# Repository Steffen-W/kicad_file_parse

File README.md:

# KiCad Parser

A comprehensive Python library for parsing and manipulating KiCad S-Expression files, including symbol libraries (.kicad_sym), footprints (.kicad_mod), worksheets (.kicad_wks), schematics (.kicad_sch), PCBs (.kicad_pcb), and related formats.

## Features

- **Full KiCad Format Support**: Parse and write KiCad symbol libraries, footprints, worksheets, schematics, and PCBs
- **Type-Safe**: Complete type hints for better IDE support and code safety
- **High-Level API**: Easy-to-use functions for common operations
- **Low-Level Access**: Direct access to S-expression data structures when needed
- **Multi-Unit Symbols**: Full support for complex symbols with multiple units and alternate representations
- **Advanced Pin Types**: Complete pin electrical type support (passive, input, output, bidirectional, tri_state, power_in, power_out, open_collector, open_emitter, free, unspecified, no_connect)
- **Hierarchical Schematics**: Support for hierarchical sheets, sheet pins, and complex project structures
- **Advanced PCB Features**: Zones with thermal reliefs and hatching patterns, advanced copper pours with complex fill settings, track arcs, board stackup definitions, and layer management
- **Modern Python**: Supports Python 3.8+
- **Zero Dependencies**: No external dependencies - includes bundled S-expression parser
- **Comprehensive Testing**: 385+ test cases ensuring reliability

## Installation

```bash
pip install kicad-parser
```

Or install from source:

```bash
git clone https://github.com/Steffen-W/kicad-parser.git
cd kicad-parser
pip install -e .
```

## Quick Start

### Loading and Modifying a Symbol Library

```python
from kicad_parser import load_symbol_library, save_symbol_library

# Load a KiCad symbol library
library = load_symbol_library("path/to/library.kicad_sym")

# Access symbols
symbol = library.symbols[0]
print(f"Symbol: {symbol.name}")

# Modify properties
symbol.set_property("Reference", "IC")
symbol.set_property("Description", "Modified with kicad-parser")

# Save changes
save_symbol_library(library, "path/to/modified_library.kicad_sym")
```

### Creating Symbols from Scratch

```python
from kicad_parser import (
    create_basic_symbol, KiCadSymbolLibrary, 
    SymbolPin, PinElectricalType, PinGraphicStyle, Position
)

# Create a new symbol library
library = KiCadSymbolLibrary(version=20211014, generator="kicad-parser")

# Create a basic resistor symbol
resistor = create_basic_symbol("R_Generic", "R", "R")

# Add pins
resistor.pins.extend([
    SymbolPin(
        electrical_type=PinElectricalType.PASSIVE,
        graphic_style=PinGraphicStyle.LINE,
        position=Position(-5.08, 0, 0),
        length=2.54,
        name="~",
        number="1"
    ),
    SymbolPin(
        electrical_type=PinElectricalType.PASSIVE,
        graphic_style=PinGraphicStyle.LINE,
        position=Position(5.08, 0, 0),
        length=2.54,
        name="~",
        number="2"
    )
])

# Add to library and save
library.add_symbol(resistor)
save_symbol_library(library, "custom_library.kicad_sym")
```

### Working with Footprints

```python
from kicad_parser import load_footprint, save_footprint, create_basic_footprint

# Load footprint
footprint = load_footprint("path/to/footprint.kicad_mod")

# Create basic footprint
new_footprint = create_basic_footprint("0805_Resistor", "R", "0805")

# Save footprint
save_footprint(new_footprint, "0805_resistor.kicad_mod")
```

### Working with Worksheets

```python
from kicad_parser import (
    load_worksheet, save_worksheet, create_basic_worksheet,
    KiCadWorksheet, WorksheetText, WorksheetRectangle, 
    Position, CornerType
)

# Load existing worksheet
worksheet = load_worksheet("path/to/worksheet.kicad_wks")

# Create basic worksheet
new_worksheet = create_basic_worksheet("My Project", "My Company")

# Create custom worksheet
custom_worksheet = KiCadWorksheet()

# Add title block rectangle
custom_worksheet.add_rectangle(
    WorksheetRectangle(
        start=Position(110.0, 5.0),
        end=Position(210.0, 35.0),
        corner=CornerType.RIGHT_BOTTOM
    )
)

# Add title text
custom_worksheet.add_text(
    WorksheetText(
        text="Project Title",
        position=Position(160.0, 20.0),
        corner=CornerType.RIGHT_BOTTOM,
        maxlen=25
    )
)

# Save worksheet
save_worksheet(custom_worksheet, "custom_worksheet.kicad_wks")
```

### Generating UUIDs

KiCad objects often require unique identifiers. Use the `generate_UUID()` function instead of creating UUIDs manually:

```python
from kicad_parser import generate_UUID, KiCadSchematic, TitleBlock

# Generate UUIDs for new objects
schematic = KiCadSchematic(
    uuid=generate_UUID(),
    title_block=TitleBlock(title="My Project")
)

# For groups, symbols, or other objects requiring UUIDs
group_id = generate_UUID()
symbol_uuid = generate_UUID()
```

**Note**: UUIDs are not generated automatically. Always use `generate_UUID()` when creating objects that require unique identifiers.

### Working with Schematics

```python
from kicad_parser import (
    load_schematic, save_schematic, create_basic_schematic,
    KiCadSchematic, Junction, Wire, Bus, SchematicSymbol,
    GlobalLabel, HierarchicalSheet, HierarchicalPin, 
    LabelShape, PinElectricalType, Position, UUID, Property, TitleBlock
)

# Load existing schematic
schematic = load_schematic("path/to/schematic.kicad_sch")

# Create basic schematic
new_schematic = create_basic_schematic("LED Blinker", "My Company")

# Create comprehensive schematic
custom_schematic = KiCadSchematic(
    title_block=TitleBlock(
        title="Custom Circuit",
        date="2024-01-01",
        revision="Rev 1.0"
    )
)

# Add junctions (connection points)
custom_schematic.junctions.append(
    Junction(
        position=Position(50.0, 50.0),
        diameter=0.36,
        uuid=UUID("junction-1")
    )
)

# Add wires (connections)
custom_schematic.wires.extend([
    Wire(
        points=[(25.4, 25.4), (50.0, 25.4)],
        uuid=UUID("wire-1")
    ),
    Wire(
        points=[(50.0, 25.4), (50.0, 50.0)],  
        uuid=UUID("wire-2")
    )
])

# Add components/symbols
custom_schematic.symbols.append(
    SchematicSymbol(
        library_id="Device:R",
        position=Position(75.0, 50.0),
        uuid=UUID("R1"),
        properties=[
            Property("Reference", "R1"),
            Property("Value", "10k"),
            Property("Footprint", "Resistor_SMD:R_0603_1608Metric")
        ]
    )
)

# Add global labels for cross-sheet connections
custom_schematic.global_labels.append(
    GlobalLabel(
        text="VCC",
        shape=LabelShape.INPUT,
        position=Position(25.4, 75.0),
        uuid=UUID("vcc-label")
    )
)

# Add hierarchical sheets for complex designs
power_sheet = HierarchicalSheet(
    position=Position(150.0, 100.0),
    size=(50.0, 40.0),
    sheet_name="Power Supply",
    file_name="power.kicad_sch",
    uuid=UUID("power-sheet")
)

# Add pins to hierarchical sheet
power_sheet.pins.append(
    HierarchicalPin(
        name="VCC_OUT",
        electrical_type=PinElectricalType.OUTPUT,
        position=Position(150.0, 110.0),
        uuid=UUID("vcc-out-pin")
    )
)

custom_schematic.sheets.append(power_sheet)

# Add bus connections for multi-signal connections
custom_schematic.buses.append(
    Bus(
        points=[(100.0, 150.0), (200.0, 150.0)],
        uuid=UUID("data-bus")
    )
)

# Save schematic
save_schematic(custom_schematic, "custom_circuit.kicad_sch")
```

### Working with PCBs (Boards)

```python
from kicad_parser import (
    load_pcb, save_pcb, create_basic_pcb,
    KiCadPCB, BoardLayer, BoardNet, GeneralSettings, Zone,
    TrackSegment, TrackVia, TrackArc, LayerType, ViaType, 
    PadConnection, UUID
)

# Load existing PCB
pcb = load_pcb("path/to/board.kicad_pcb")

# Create basic PCB
new_pcb = create_basic_pcb()

# Create comprehensive PCB
custom_pcb = KiCadPCB(
    version=20230121,
    generator="kicad-parser",
    general=GeneralSettings(thickness=1.6)
)

# Define standard layer stackup
layers = [
    BoardLayer(ordinal=0, canonical_name="F.Cu", layer_type=LayerType.SIGNAL, user_name="Front Copper"),
    BoardLayer(ordinal=31, canonical_name="B.Cu", layer_type=LayerType.SIGNAL, user_name="Back Copper"),
    BoardLayer(ordinal=36, canonical_name="B.SilkS", layer_type=LayerType.USER, user_name="B.Silkscreen"),
    BoardLayer(ordinal=37, canonical_name="F.SilkS", layer_type=LayerType.USER, user_name="F.Silkscreen"),
    BoardLayer(ordinal=44, canonical_name="Edge.Cuts", layer_type=LayerType.USER, user_name="Edge Cuts"),
]
custom_pcb.layers = layers

# Create nets
nets = [
    BoardNet(ordinal=0, name=""),  # Unconnected net
    BoardNet(ordinal=1, name="GND"),
    BoardNet(ordinal=2, name="VCC"),
    BoardNet(ordinal=3, name="SIGNAL_DATA"),
]
custom_pcb.nets = nets

# Add track segments (copper traces)
custom_pcb.track_segments.extend([
    TrackSegment(
        start=(10.0, 10.0),
        end=(20.0, 10.0),
        width=0.25,  # 0.25mm width
        layer="F.Cu",
        net=1,  # GND net
        uuid=UUID("track-gnd-1")
    ),
    TrackSegment(
        start=(10.0, 15.0),
        end=(20.0, 15.0),
        width=0.25,
        layer="F.Cu",
        net=2,  # VCC net
        uuid=UUID("track-vcc-1")
    )
])

# Add vias (layer connections)
custom_pcb.track_vias.extend([
    TrackVia(
        position=(15.0, 10.0),
        size=0.8,      # Via diameter
        drill=0.4,     # Drill diameter
        layers=("F.Cu", "B.Cu"),
        net=1,         # GND net
        via_type=ViaType.THROUGH,
        uuid=UUID("via-gnd-1")
    ),
    TrackVia(
        position=(15.0, 15.0),
        size=0.8,
        drill=0.4,
        layers=("F.Cu", "B.Cu"),
        net=2,         # VCC net
        via_type=ViaType.THROUGH,
        uuid=UUID("via-vcc-1")
    )
])

# Add copper zones/pours
custom_pcb.zones.append(
    Zone(
        net=1,  # GND net
        net_name="GND",
        layers=["F.Cu"],
        polygon_points=[
            (5.0, 5.0), (25.0, 5.0), (25.0, 25.0), (5.0, 25.0)
        ],
        connect_pads=PadConnection.THERMAL,
        min_thickness=0.254,
        uuid=UUID("ground-zone-1")
    )
)

# Add curved traces (track arcs)
custom_pcb.track_arcs.append(
    TrackArc(
        start=(30.0, 10.0),
        mid=(32.0, 12.0),
        end=(34.0, 10.0),
        width=0.25,
        layer="F.Cu",
        net=3,  # SIGNAL_DATA net
        uuid=UUID("arc-signal-1")
    )
)

# Save PCB
save_pcb(custom_pcb, "custom_board.kicad_pcb")
```

## API Reference

### High-Level Functions

#### File I/O

- `load_symbol_library(filepath)` → `KiCadSymbolLibrary`
- `save_symbol_library(library, filepath)` → `None`
- `load_footprint(filepath)` → `KiCadFootprint`
- `save_footprint(footprint, filepath)` → `None`
- `load_worksheet(filepath)` → `KiCadWorksheet`
- `save_worksheet(worksheet, filepath)` → `None`
- `load_schematic(filepath)` → `KiCadSchematic`
- `save_schematic(schematic, filepath)` → `None`
- `load_pcb(filepath)` → `KiCadPCB`
- `save_pcb(pcb, filepath)` → `None`
- `load_kicad_file(filepath)` → `KiCadObject` (auto-detects type)
- `save_kicad_file(obj, filepath)` → `None`

#### Creation Helpers

- `create_basic_symbol(name, reference, value)` → `KiCadSymbol`
- `create_basic_footprint(name, reference, value)` → `KiCadFootprint`
- `create_basic_worksheet(title, company)` → `KiCadWorksheet`
- `create_basic_schematic(title, company)` → `KiCadSchematic`
- `create_basic_pcb()` → `KiCadPCB`

#### Utilities

- `detect_file_type(content)` → `str`
- `validate_kicad_file(filepath)` → `dict`
- `convert_file(input_path, output_path, modifier_func=None)` → `None`
- `str_to_sexpr(content)` → `SExpr` - Convert string content to S-expression
- `sexpr_to_str(sexpr, pretty_print=True)` → `str` - Convert S-expression to formatted string
- `generate_UUID()` → `UUID` - Generate a new random UUID for KiCad objects

### Core Classes

#### Symbol Library (`KiCadSymbolLibrary`)

- `symbols: List[KiCadSymbol]` - List of symbols in library
- `version: int` - KiCad format version
- `generator: str` - Generator identifier
- `get_symbol(name)` → `Optional[KiCadSymbol]`
- `add_symbol(symbol)` → `None`
- `remove_symbol(name)` → `bool`

*Detailed S-expression format reference: [sexp-intro.md](doc/file-formats/sexp-intro.md)*

#### Symbol (`KiCadSymbol`)

- `name: str` - Symbol name
- `extends: Optional[str]` - Parent symbol for inheritance (symbol extends/parent support)
- `pin_numbers_hide: bool` - Hide pin numbers
- `pin_names_hide: bool` - Hide pin names  
- `pin_names_offset: float` - Pin name offset distance (advanced pin properties)
- `in_bom: bool` - Include in bill of materials
- `on_board: bool` - Export to PCB
- `properties: List[SymbolProperty]` - Symbol properties
- `pins: List[SymbolPin]` - Symbol pins with all electrical types
- `units: List[SymbolUnit]` - Symbol units for multi-unit symbols
- `rectangles: List[SymbolRectangle]` - Graphic rectangles
- `circles: List[SymbolCircle]` - Graphic circles
- `arcs: List[SymbolArc]` - Graphic arcs
- `beziers: List[SymbolBezier]` - Bézier curves
- `polylines: List[SymbolPolyline]` - Multi-point lines
- `texts: List[SymbolText]` - Text elements
- `get_property(key)` → `Optional[SymbolProperty]`
- `set_property(key, value, **kwargs)` → `None`
- `remove_property(key)` → `bool`

*Detailed S-expression format reference: [sexp-intro.md](doc/file-formats/sexp-intro.md)*

#### Footprint (`KiCadFootprint`)

- `library_link: str` - Link to symbol library
- `pads: List[FootprintPad]` - Footprint pads with custom primitives and complex shapes support
- `zones: List[Zone]` - Footprint-level copper zones
- `keepout_zones: List[Zone]` - Footprint keepout areas with configurable restrictions
- `groups: List[Group]` - Footprint object grouping for organization
- `net_tie_pad_groups: List[str]` - Net-tie pad group definitions for shorts allowed between pads
- `private_layers: List[str]` - Private layer definitions for footprint-specific layers
- `texts: List[FootprintText]` - Text elements
- `lines: List[FootprintLine]` - Graphic lines
- `rectangles: List[FootprintRectangle]` - Graphic rectangles
- `circles: List[FootprintCircle]` - Graphic circles
- `arcs: List[FootprintArc]` - Graphic arcs
- `polygons: List[FootprintPolygon]` - Graphic polygons
- `model: Footprint3DModel` - Advanced 3D model with positioning, scaling, rotation, opacity, and visibility control
- `position: Position` - Footprint position
- `layer: str` - Footprint placement layer
- `locked: bool` - Footprint lock status
- `attributes: FootprintAttributes` - Footprint attributes (SMD, through-hole, exclude from BOM/board)

*Detailed S-expression format reference: [sexp-intro.md](doc/file-formats/sexp-intro.md)*

#### Worksheet (`KiCadWorksheet`)

- `version: int` - KiCad format version
- `generator: str` - Generator identifier
- `setup: WorksheetSetup` - Page setup configuration
- `lines: List[WorksheetLine]` - Line elements
- `rectangles: List[WorksheetRectangle]` - Rectangle elements
- `polygons: List[WorksheetPolygon]` - Polygon elements
- `texts: List[WorksheetText]` - Title block text elements
- `bitmaps: List[WorksheetBitmap]` - Image elements
- `add_line(line)` → `None`
- `add_rectangle(rectangle)` → `None`
- `add_polygon(polygon)` → `None`
- `add_text(text)` → `None`
- `add_bitmap(bitmap)` → `None`

*Detailed S-expression format reference: [sexp-worksheet.md](doc/file-formats/sexp-worksheet.md)*

#### Schematic (`KiCadSchematic`)

- `version: int` - KiCad format version
- `generator: str` - Generator identifier
- `uuid: UUID` - Schematic unique identifier
- `page_settings: PageSettings` - Paper size and orientation
- `title_block: TitleBlock` - Title block information
- `lib_symbols: List[KiCadSymbol]` - Symbol library definitions
- `junctions: List[Junction]` - Connection junctions
- `no_connects: List[NoConnect]` - Unused pin markers
- `wires: List[Wire]` - Wire connections
- `buses: List[Bus]` - Bus connections
- `symbols: List[SchematicSymbol]` - Component instances
- `global_labels: List[GlobalLabel]` - Cross-sheet labels
- `hierarchical_labels: List[HierarchicalLabel]` - Sheet connection labels
- `local_labels: List[LocalLabel]` - Wire/bus labels
- `sheets: List[HierarchicalSheet]` - Sub-schematic sheets
- `texts: List[SchematicText]` - Text annotations
- `polylines: List[Polyline]` - Graphical lines
- `images: List[Image]` - Embedded images

*Detailed S-expression format reference: [sexp-schematic.md](doc/file-formats/sexp-schematic.md)*

### Data Types

#### Core S-Expression Types

- `Position(x, y, angle, layer)` - Position identifier with coordinates, rotation, and optional layer
- `CoordinatePoint(x, y)` - Single coordinate point with X/Y values
- `CoordinatePointList(points)` - Point list for polygons and curves with XY coordinate pairs
- `Stroke(width, type, color)` - Stroke definition with line styles, width, and color
- `StrokeType` - DEFAULT, NONE, SOLID, DASH, DOT, DASH_DOT, DASH_DOT_DOT - Line style types
- `TextEffects(font, justify, hide, mirror)` - Complete text formatting with alignment and visibility
- `Font(size, thickness, bold, italic, line_spacing, face)` - Font definition with all typography attributes
- `Fill(type, color)` - Fill definition with type and color
- `FillType` - NONE, OUTLINE, BACKGROUND - Fill style types
- `PageSettings(paper, width, height, portrait)` - Page configuration with size and orientation
- `TitleBlock(title, date, revision, company, comment_1_4)` - Title block with project information
- `Property(key, value, id, position, effects, show_name, do_not_autoplace)` - Properties with positioning and display control
- `UUID(uuid_string)` - Universally unique identifiers for object tracking
- `Image(position, scale, layer, data, uuid)` - Embedded PNG/bitmap images with positioning and Base64 data
- `Color(r, g, b, a)` - RGBA color definition with transparency support
- `Justify` - LEFT, CENTER, RIGHT, TOP, BOTTOM - Text alignment options
- `PaperSize` - A4, A3, A2, A1, A0, LETTER, LEGAL, TABLOID, USR - Standard paper sizes

#### Board-Specific Types

- `CANONICAL_LAYER_NAMES` - All 58 standard KiCad layers (F.Cu, B.Cu, F.SilkS, etc.)

#### Symbol Types

- `SymbolPin(electrical_type, graphic_style, position, length, name, number)` - Symbol pins with all electrical types
- `SymbolProperty(key, value, id, position, effects)` - Symbol properties with positioning
- `SymbolUnit(name, unit_id)` - Multi-unit symbol definitions for complex components
- `SymbolArc(start, mid, end, stroke, fill, uuid)` - Graphic arc elements
- `SymbolCircle(center, radius, stroke, fill, uuid)` - Graphic circle elements  
- `SymbolRectangle(start, end, stroke, fill, uuid)` - Graphic rectangle elements
- `SymbolBezier(points, stroke, fill, uuid)` - Bézier curve elements
- `SymbolPolyline(points, stroke, fill, uuid)` - Multi-point line elements
- `SymbolText(text, position, angle, effects, uuid)` - Text annotations and labels

#### Pin Types

- `PinElectricalType` - PASSIVE, INPUT, OUTPUT, BIDIRECTIONAL, TRI_STATE, POWER_IN, POWER_OUT, OPEN_COLLECTOR, OPEN_EMITTER, FREE, UNSPECIFIED, NO_CONNECT
- `PinGraphicStyle` - LINE, INVERTED, CLOCK, INVERTED_CLOCK, INPUT_LOW, CLOCK_LOW, OUTPUT_LOW, EDGE_CLOCK_HIGH, NONLOGIC

#### Footprint Types

- `FootprintPad(number, type, shape, size, drill, layers, position, net, uuid)` - Footprint pads with all pad types and shapes
- `FootprintText(type, text, position, layer, effects, uuid)` - Footprint text elements (reference, value, user)
- `FootprintLine(start, end, layer, width, uuid)` - Footprint graphic lines
- `FootprintRectangle(start, end, layer, stroke, fill, uuid)` - Footprint graphic rectangles
- `FootprintCircle(center, end, layer, stroke, fill, uuid)` - Footprint graphic circles
- `FootprintArc(start, mid, end, layer, stroke, uuid)` - Footprint graphic arcs
- `FootprintPolygon(points, layer, stroke, fill, uuid)` - Footprint graphic polygons
- `FootprintAttributes(type, board_only, exclude_from_pos_files, exclude_from_bom)` - Footprint placement attributes
- `FootprintOptions(clearance, solder_mask_margin, solder_paste_margin, zone_connect, thermal_width, thermal_gap)` - Advanced footprint options and clearances
- `CustomPadOptions(clearance, solder_mask_margin, solder_paste_margin, thermal_gap)` - Custom pad-specific options
- `FootprintPrimitives(primitives_list)` - Custom pad primitive shapes and geometries
- `CustomPadPrimitives(primitives_list)` - Advanced custom pad shape definitions
- `Net(code, name)` - Network connection definitions for pads
- `Drill(diameter, oval_width)` - Drill hole specifications with oval support
- `DrillDefinition(size, offset, shape)` - Complete drill definition with positioning
- `PadAttribute(type, value)` - Pad electrical and mechanical attributes
- `KeepoutSettings(tracks, vias, pads, copperpour, footprints)` - Keepout zone restrictions
- `KeepoutZone(layers, settings, polygon, uuid)` - Keepout areas with configurable restrictions
- `FootprintGroup(name, members, uuid)` - Footprint object grouping for organization
- `Model3D(filename, offset, scale, rotate)` - 3D model positioning and transformation
- `Footprint3DModel(filename, offset, scale, rotate, opacity, hide)` - 3D model with full control
- `FootprintType` - SMD, THROUGH_HOLE, EXCLUDE_FROM_POS_FILES, EXCLUDE_FROM_BOM - Footprint classifications
- `FootprintTextType` - REFERENCE, VALUE, USER - Text element types

#### Worksheet Types

- `WorksheetSetup(textsize, linewidth, textlinewidth, margins)` - Page setup with text sizes and margins
- `WorksheetLine(start, end, name, linewidth, repeat, increment)` - Lines with optional repetition and increments
- `WorksheetRectangle(start, end, name, linewidth, repeat, increment)` - Rectangles for borders and frames
- `WorksheetPolygon(points, name, linewidth, repeat, increment)` - Custom polygon shapes with coordinate points
- `WorksheetText(text, position, corner, name, maxlen, maxheight, font, justify)` - Title block text with positioning and limits
- `WorksheetBitmap(position, scale, data, name, repeat, increment)` - Embedded bitmap images with Base64 data
- `CornerType` - LEFT_TOP, LEFT_BOTTOM, RIGHT_BOTTOM, RIGHT_TOP - Position reference points

#### Schematic Types

- `Junction(position, diameter, color, uuid)` - Connection junction points
- `BusEntry(position, size, stroke, uuid)` - Bus connection entries with angle and direction
- `Wire(points, stroke, uuid)` - Electrical wire connections with multi-point routing
- `Bus(points, stroke, uuid)` - Multi-signal bus connections with stroke styling
- `SchematicText(text, position, effects, exclude_from_sim, uuid)` - Text annotations with simulation control
- `LocalLabel(text, position, effects, exclude_from_sim, uuid)` - Wire/bus name labels
- `GlobalLabel(text, shape, position, fields, properties, uuid)` - Cross-sheet labels with custom fields
- `HierarchicalLabel(text, shape, position, effects, uuid)` - Sheet connection labels
- `SchematicSymbol(library_id, position, unit, convert, exclude_from_sim, properties, instances)` - Component instances with simulation control
- `SheetInstance(path, page, uuid)` - Sheet instance definitions for hierarchical designs
- `SheetProject(file, name, description)` - Project information for sheet references
- `HierarchicalSheet(position, size, sheet_name, file_name, pins, project, instances, uuid)` - Sub-schematic sheets with project data
- `HierarchicalPin(name, electrical_type, position, uuid)` - Sheet connection pins
- `RootSheetInstance(project, page, uuid)` - Root sheet instance for project hierarchy
- `LabelShape` - INPUT, OUTPUT, BIDIRECTIONAL, TRI_STATE, PASSIVE - Label and pin shapes
- `NoConnect(position, uuid)` - Unused pin markers
- `Polyline(points, stroke, uuid)` - Graphical line drawings
- `Image(position, scale, layer, data, uuid)` - Embedded PNG images with Base64 data

#### PCB Types

- `KiCadPCB(version, generator, general, paper, layers, setup, nets, footprints, track_segments, track_vias, track_arcs, zones, groups)` - Complete PCB definition with all elements
- `GeneralSettings(thickness, legacy_teardrops)` - Board general settings and thickness
- `BoardLayer(ordinal, canonical_name, layer_type, user_name)` - PCB layer definition with all 58 standard layers
- `BoardSetup(stackup, design_rules, defaults, diff_pair_dimensions, pad_to_mask_clearance)` - Complete PCB setup with design rules and stackup
- `BoardNet(ordinal, name)` - Electrical net definition with net classes
- `TrackSegment(start, end, width, layer, net, tstamp, uuid)` - Copper trace segment with timestamps
- `TrackVia(position, size, drill, layers, net, via_type, remove_unused_layers, keep_end_layers, uuid)` - Via with advanced layer management
- `TrackArc(start, mid, end, width, layer, net, tstamp, uuid)` - Curved copper trace with arc geometry
- `Zone(net, net_name, layers, tstamp, name, hatch, priority, connect_pads, min_thickness, filled_polygons, fill_segments)` - Complete zone with fill geometry
- `ZoneConnect(clearance, min_thickness, thermal_gap, thermal_bridge_width)` - Zone connection settings
- `ZoneFillSettings(yes, mode, thermal_gap, thermal_bridge_width, smoothing, island_removal_mode, island_area_min)` - Zone fill configuration
- `Group(name, id, locked, members, uuid)` - Object grouping with locking and member tracking
- `Net(ordinal, name, uuid)` - Net definition with UUID tracking
- `Dimension(type, layer, tstamp, pts, height, orientation, leader_length, text_position, format, style, uuid)` - PCB dimensions and measurements
- `LayerType` - SIGNAL, POWER, MIXED, JUMPER, USER - Layer type classification
- `ViaType` - THROUGH, BLIND, MICRO - Via type specification with advanced drilling
- `PadConnection` - INHERITED, SOLID, THERMAL_RELIEFS, THRU_HOLE_ONLY, NONE - Zone connection styles
- `PadShape` - CIRCLE, RECT, OVAL, TRAPEZOID, ROUNDRECT, CUSTOM - Pad shape definitions
- `DrillShape` - CIRCLE, OVAL - Drill hole shapes

*Detailed S-expression format reference: [sexp-pcb.md](doc/file-formats/sexp-pcb.md)*

#### Design Rules Types

- `KiCadDesignRules(version, generator, rules)` - Complete design rules definition with all DRC rules
- `DesignRule(name, layer, constraint, condition, severity)` - Individual design rule with conditions and constraints
- `DesignRuleConstraint(type, value, opt_value, comment)` - Design rule constraint with value ranges
- `ConstraintValue(min, opt, max, units)` - Constraint value with optional minimum, optimal, and maximum values
- `ConstraintType` - CLEARANCE, TRACK_WIDTH, VIA_SIZE, DRILL_SIZE, LENGTH, SKEW, DISALLOW - Constraint classifications
- `DRCSeverity` - ERROR, WARNING, IGNORE, EXCLUSION - DRC violation severity levels

*Detailed S-expression format reference: [sexp-design-rules.md](doc/file-formats/sexp-design-rules.md)*

#### Graphics Types

- `GraphicalText(text, position, angle, layer, effects, uuid)` - Text elements with positioning and styling
- `GraphicalLine(start, end, layer, stroke, uuid)` - Straight line segments with stroke styling
- `GraphicalRectangle(start, end, layer, stroke, fill, uuid)` - Rectangle shapes with fill and stroke
- `GraphicalCircle(center, radius, layer, stroke, fill, uuid)` - Circle shapes with customizable appearance
- `GraphicalArc(start, mid, end, layer, stroke, uuid)` - Arc segments defined by three points
- `GraphicalPolygon(points, layer, stroke, fill, uuid)` - Multi-point polygon shapes
- `GraphicalBezier(points, layer, stroke, fill, uuid)` - Bézier curve segments for smooth curves
- `GraphicalTextBox(text, position, size, angle, layer, effects, stroke, uuid)` - Text with background box
- `Dimension(type, layer, pts, height, orientation, leader_length, format, style, uuid)` - PCB measurements and annotations
- `DimensionFormat(prefix, suffix, units, units_format, precision, suppress_zeros)` - Dimension text formatting
- `DimensionStyle(thickness, arrow_length, text_position_mode, extension_height, text_frame)` - Dimension appearance settings

#### Design Rules Types

- `KiCadDesignRules(version, generator, rules)` - Complete design rules definition with all DRC rules
- `DesignRule(name, layer, constraint, condition, severity)` - Individual design rule with conditions and constraints
- `DesignRuleConstraint(type, value, opt_value, comment)` - Design rule constraint with value ranges
- `ConstraintValue(min, opt, max, units)` - Constraint value with optional minimum, optimal, and maximum values
- `ConstraintType` - CLEARANCE, TRACK_WIDTH, VIA_SIZE, DRILL_SIZE, LENGTH, SKEW, DISALLOW - Constraint classifications
- `DRCSeverity` - ERROR, WARNING, IGNORE, EXCLUSION - DRC violation severity levels

## Examples

The `examples/` directory contains complete working examples:

- `basic_usage.py` - Loading, modifying, and saving symbol libraries
- `create_symbol.py` - Creating custom symbols and libraries from scratch
- `file_conversion.py` - File validation and conversion utilities
- `worksheet_example.py` - Creating custom worksheets and page layouts
- `schematic_example.py` - Creating comprehensive schematics with all element types
- `pcb_example.py` - Creating PCBs with layers, nets, tracks, and vias
- `file_comparison.py` - Comprehensive utility for comparing KiCad files
- `round_trip_test.py` - Parser accuracy validation through round-trip testing

### File Comparison Tool

A comprehensive utility for comparing KiCad files with multiple comparison modes and built-in demo functionality:

#### Comparison Modes

- **Exact Comparison**: Files must be completely identical (content, order, formatting)
- **Structural Comparison**: Same content, order doesn't matter (uses KiCad parser for semantic comparison)
- **Text Comparison**: Plain text comparison with optional whitespace normalization
- **Comprehensive Comparison**: Runs all methods and shows detailed results with similarity scores

#### Usage

```bash
# Command line usage
python examples/file_comparison.py file1.kicad_sch file2.kicad_sch

# Run without arguments to see interactive demo
python examples/file_comparison.py

# Programmatic usage
from examples.file_comparison import compare_files_exact, compare_files_structural
from kicad_parser.file_comparison_utils import ComparisonResult

result = compare_files_exact("file1.kicad_sch", "file2.kicad_sch")
print(f"Equal: {result.are_equal}, Similarity: {result.similarity_score:.2%}")

# Comprehensive comparison with detailed output
results = compare_files_comprehensive("original.kicad_sch", "modified.kicad_sch")
for method, result in results.items():
    print(f"{method}: {result}")
```

#### Available Functions

- `compare_files_exact()` → Perfect match comparison
- `compare_files_structural()` → Semantic content comparison  
- `compare_files_text()` → Text-based comparison with whitespace options
- `compare_files_comprehensive()` → All methods with detailed output

### Round-Trip Test

Validates parser accuracy by loading and re-saving KiCad files, then comparing the results:

```bash
# Run comprehensive accuracy test
python examples/round_trip_test.py

# Output shows parser fidelity:
# ROUND-TRIP TEST SUMMARY
# Accuracy Results:
#    Exact Match: 1/22 perfect (4.5%), avg similarity: 9.1%
#    Structural: 20/22 perfect (90.9%), avg similarity: 97.2%
#    Text (with whitespace): 1/22 perfect (4.5%), avg similarity: 9.1%
#    Text (normalized): 1/22 perfect (4.5%), avg similarity: 16.2%
```

This example demonstrates the high fidelity of the KiCad parser by testing all files in `examples/test_data/` and reporting conversion accuracy statistics.

Run examples:

```bash
cd examples
python basic_usage.py
python create_symbol.py
python file_conversion.py
python worksheet_example.py
python schematic_example.py
python file_comparison.py  # Runs demo automatically
python round_trip_test.py  # Validates parser accuracy
```

## Development

### Setup Development Environment

```bash
git clone https://github.com/Steffen-W/kicad-parser.git
cd kicad-parser
pip install -e ".[dev]"
```

### Running Tests

```bash
# Run all tests
pytest

# Run with coverage
pytest --cov=kicad_parser

# Generate coverage report
pytest --cov=kicad_parser --cov-report=html
pytest --cov=kicad_parser --cov-report=term-missing
```

### Documentation

Generate API documentation with Sphinx:

```bash
pip install -e .[docs]
python docs/build-docs.py
```

Open `docs/_build/html/index.html` in your browser. Use `python docs/build-docs.py pdf` for other formats.

### Code Quality

```bash
# Install required tools
pip install black isort flake8 mypy
npm install -g pyright

# Format entire codebase with black
black .

# Sort imports for entire codebase
isort .

# Lint code with flake8
flake8 kicad_parser

# Static type checking with Pyright
pyright

# Static type checking with mypy
mypy kicad_parser
```

## Implementation Reference

This library was developed based on the official KiCad S-Expression file format documentation:
**<https://dev-docs.kicad.org/en/file-formats/sexpr-intro/index.html>**

The data schema for parsing KiCad files is sourced from:
**<https://gitlab.com/kicad/services/kicad-dev-docs/-/tree/master/content/file-formats>**

The DRC (Design Rule Checking) implementation is based on:
**<https://docs.kicad.org/master/id/pcbnew/pcbnew_advanced.html#custom-design-rules>**

The Python functions and data structures closely follow the specifications described in the KiCad documentation to ensure maximum compatibility and correctness when parsing and generating KiCad files.

## S-Expression Format Support

This library provides **complete implementation** of the KiCad S-Expression format specification with support for all positioning, styling, layering, and embedded content elements.

## Module Structure

The library is organized into focused modules to avoid circular dependencies and provide clear separation of concerns:

- **`kicad_common.py`** - Common classes and utilities (UUID, Position, SExpr parsing, etc.)
- **`kicad_symbol.py`** - Symbol library and symbol definitions
- **`kicad_board.py`** - Footprint definitions and board-level footprint components
- **`kicad_board_elements.py`** - Shared board elements (zones, connections) used by both footprints and PCBs
- **`kicad_pcb.py`** - PCB definitions, layers, nets, tracks, and board-specific components
- **`kicad_schematic.py`** - Schematic definitions and hierarchical designs
- **`kicad_worksheet.py`** - Worksheet/template definitions for documentation
- **`kicad_graphics.py`** - Graphical primitives (lines, arcs, text, etc.)
- **`kicad_design_rules.py`** - Design rule checking (DRC) definitions
- **`kicad_file.py`** - File I/O operations and format detection
- **`kicad_main.py`** - High-level convenience functions and examples

The separation of board elements allows both footprints and PCBs to use shared zone and connection classes without circular import issues.

## Supported File Formats

- **Symbol Libraries** (`.kicad_sym`) - Complete support with all S-Expression features (see [doc/file-formats/sexp-intro.md](doc/file-formats/sexp-intro.md))
- **Footprints** (`.kicad_mod`) - Complete support with advanced pad features, includes legacy `module` format (see [doc/file-formats/sexp-intro.md](doc/file-formats/sexp-intro.md))
- **Worksheets** (`.kicad_wks`) - Complete support with custom layouts (see [doc/file-formats/sexp-worksheet.md](doc/file-formats/sexp-worksheet.md))
- **Schematics** (`.kicad_sch`) - Complete support with hierarchical designs, buses, and all element types (see [doc/file-formats/sexp-schematic.md](doc/file-formats/sexp-schematic.md))
- **PCBs** (`.kicad_pcb`) - Complete support with layers, nets, tracks, vias, and zones (see [doc/file-formats/sexp-pcb.md](doc/file-formats/sexp-pcb.md))
- **Design Rules** (`.kicad_dru`) - Complete support for design rule checking (see [doc/file-formats/sexp-design-rules.md](doc/file-formats/sexp-design-rules.md))

## Version Compatibility

This library provides backward compatibility for different KiCad S-Expression formats without requiring explicit version detection. Supports KiCad 5.x+ with automatic format modernization during parsing while preserving the original version numbers when saving.

## Contributing

Contributions are welcome! Please:

1. Fork the repository
2. Create a feature branch (`git checkout -b feature/amazing-feature`)
3. Make your changes with tests
4. Run the test suite (`pytest`)
5. Commit your changes (`git commit -m 'Add amazing feature'`)
6. Push to the branch (`git push origin feature/amazing-feature`)
7. Open a Pull Request

## License

This project is licensed under the MIT License - see the [LICENSE](LICENSE) file for details.

## Acknowledgments

- Based on the official KiCad S-Expression documentation
- Includes a modified version of `sexpdata` for S-expression parsing
- Inspired by the KiCad development community

---

**Documentation**: [KiCad S-Expression Format](https://dev-docs.kicad.org/en/file-formats/sexpr-intro/index.html)  
**Issues**: [GitHub Issues](https://github.com/Steffen-W/kicad-parser/issues)  
**Repository**: [GitHub Repository](https://github.com/Steffen-W/kicad-parser)

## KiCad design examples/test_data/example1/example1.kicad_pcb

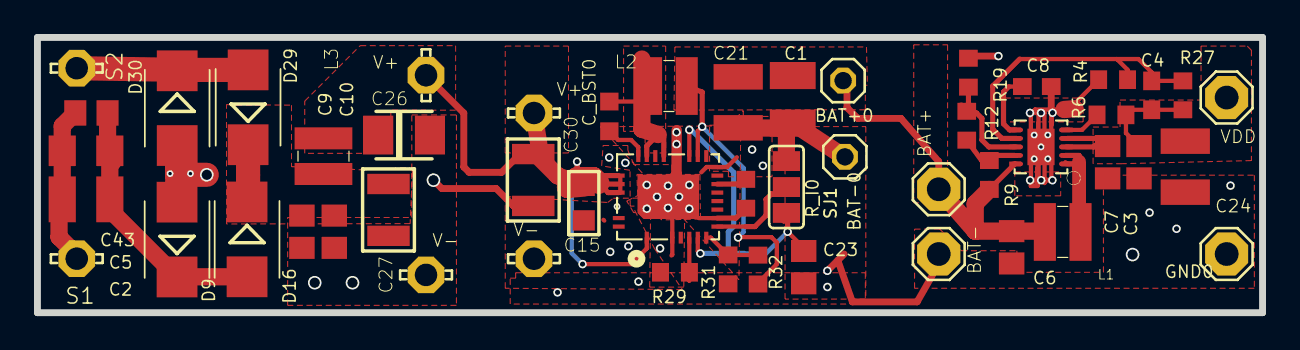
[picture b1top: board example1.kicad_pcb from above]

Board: 2 copper layers, 72.1 x 16.2 mm, 51 parts (0 on the bottom side), 21 nets.

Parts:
BAT+0: 1X01
BAT-0: 1X01
C1: 100uF 10V; C1210
C2: C-EUC1210; C1210
C3, C7: 10uF X5R 10V RS.:846-7293; C0805
C4: 18pF 50V RS Best.-Nr. 147-415; C0603
C5: C-EUC1206; C1206
C6: X5R, 22μF 6,3V RS Best.-Nr. 144-8498; C0805
C8: X7R, 10nF 10V RS Best.-Nr.839-2798; C0603
C9, C10: C-EUC0805; C0805
C15: RS Best.-Nr. 915-9457 100nF 100V X7R; C0805
C21: 22uF RS Best.-Nr. 515-8479; C1210K
C23: 1uF RS Best.-Nr. 146-4318; C0805
C24: 100uF 10V RS Best.-Nr. 885-1960; C1210K
C26: RS Best.-Nr. 699-2882 220nF 50V; C3528-21_T
C27, C30: RS Best.-Nr. 181-9969 4,7uF 100V X7R; C1210
C43: 0 Ohm; C0805
C_BST0: 100nF RS Best.-Nr. 904-0158; C0603K
D9, D16, D29, D30: Vishay VS-2EJH02-M3/6B SMT Diode, 200V 2A, 2-Pin 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; SMB
GND0: SE14
GND_HS0: SE14
L1, L2, L3: WE-MAPI_3020; WE-MAPI_3015_3020
LSP1, LSP2, LSP3, LSP4: LSP13
R4: 100k/ neu 220k; R0603
R6: 100k; R0603
R9: 1Mega; R0603
R12: 8,2k/ neu 910k; R0603
R19: 8,2k/ neu 330k; R0603
R27: 910/ neu 820k; R0603
R29: 75k; R0603
R31: NC/3k; R0603
R32: 0 bei fix output/ 100k; R0603
R_I0: 6,8k; R0603
S1, S2: LSP13
SJ1: SJ2W; SJ_2
U$2: TPS61230
U$6: LTC7103QFN; LTC7103
UNK5V_OUT0: SE14
U_HS0: SE14

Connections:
/5V DC/DC Wandler für Last TPS61230/V_OUT_TPS61230: C3.1, C4.1, C7.1, C24.1, R6.2, R27.2, U$2.P$3 (V_OUT), U$2.P$3_B (V_OUT), U$2.P$4 (V_OUT), U$2.P$4_B (V_OUT), UNK5V_OUT0.MP
/Anpassnetzwerk/ANT_2: C2.1, C5.1, C43.1, S1.MP
/Anpassnetzwerk/ANT_2222: C2.2, C5.2, C43.2, D9.C, D16.A
/Anpassnetzwerk/ANT_GND_2: D29.A, D30.C, S2.MP
/LiFePo Lader LTC7103/INTV_CC: C23.1, SJ1.3, U$6.INTV_CC, U$6.I_TH
/LiFePo Lader LTC7103/V_AACCC: C15.2, C26.+, C30.2, L3.2, LSP1.MP, LSP2.MP, U$6.RUN, U$6.V_IN_1 (VIN), U$6.V_IN_2 (VIN), U$6.V_IN_3 (VIN)
GND: BAT-0.1, C1.2, C3.2, C6.2, C7.2, C8.2, C9.2, C10.2, C15.1, C21.2, C23.2, C24.2, C26.-, C27.1, C30.1, D9.A, D30.A, GND0.MP, GND_HS0.MP, LSP3.MP, LSP4.MP, R4.1, R19.1, R29.1, R31.1, R_I0.1, SJ1.1, U$2.P$110 (GND), U$2.P$111 (GND), U$2.P$112 (GND), U$2.P$113 (GND), U$2.P$114 (GND), U$2.P$115 (GND), U$2.P$116 (GND), U$2.P$117 (GND), U$2.P$118 (GND), U$6.OVLO, U$6.PGND_1 (PGND), U$6.PGND_2 (PGND), U$6.PGND_3 (PGND), U$6.PLLIN/MODE, U$6.SGND, U$6.V_PROG1 (V_PROG_1)
unnamed: C4.2, R4.2, R27.1, U$2.P$7 (FB), U$2.P$7_B (FB)
unnamed: C8.1, U$2.P$6 (SS), U$2.P$6_B (SS)
unnamed: C_BST0.1, U$6.BOOST
unnamed: C_BST0.2, L2.1, U$6.SW_1 (SW), U$6.SW_2 (SW), U$6.SW_3 (SW)
unnamed: L1.2, U$2.P$1 (SW), U$2.P$1_B (SW), U$2.P$2 (SW), U$2.P$2_B (SW)
unnamed: R6.1, U$2.P$5 (PG), U$2.P$5_B (PG)
unnamed: R12.1, R19.2, U$2.P$8 (HYS), U$2.P$8_B (HYS)
unnamed: R9.1, R12.2, U$2.P9_B (EN), U$2.P$9 (EN)
unnamed: R29.2, U$6.R_IND
unnamed: R31.2, R32.1, U$6.V_FB
unnamed: R_I0.2, U$6.I_CTRL
unnamed: SJ1.2, U$6.FREQ
U_BATT+: BAT+0.1, C1.1, C6.1, C21.1, L1.1, L2.2, R9.2, R32.2, U$2.P$10 (V_IN), U$2.P$10_B (V_IN), U$6.EXTV_CC, U_HS0.MP
V_AA: C9.1, C10.1, C27.2, D16.C, D29.C, L3.1

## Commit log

2025-09-10 init
2025-09-10 add examples
2025-09-11 add file compare
2025-09-11 add round_trip_test
2025-09-11 clean up code
2025-09-12 Generate documentation with Sphinx
2025-09-17 add kicad_parserv2
2025-09-18 add new parser
2025-09-20 parse with cursor
